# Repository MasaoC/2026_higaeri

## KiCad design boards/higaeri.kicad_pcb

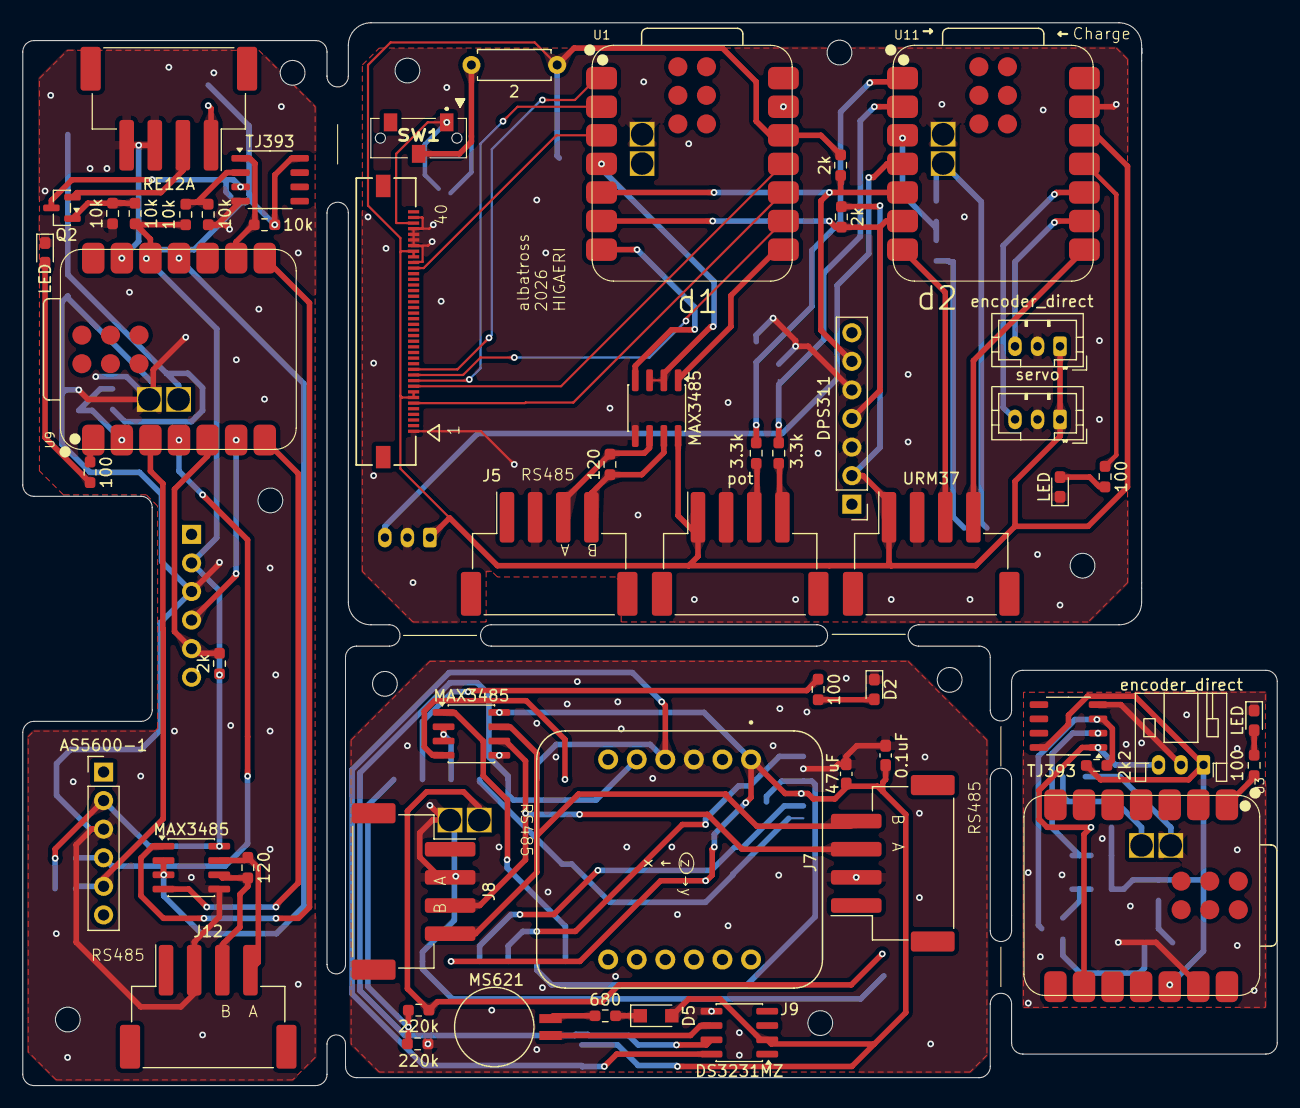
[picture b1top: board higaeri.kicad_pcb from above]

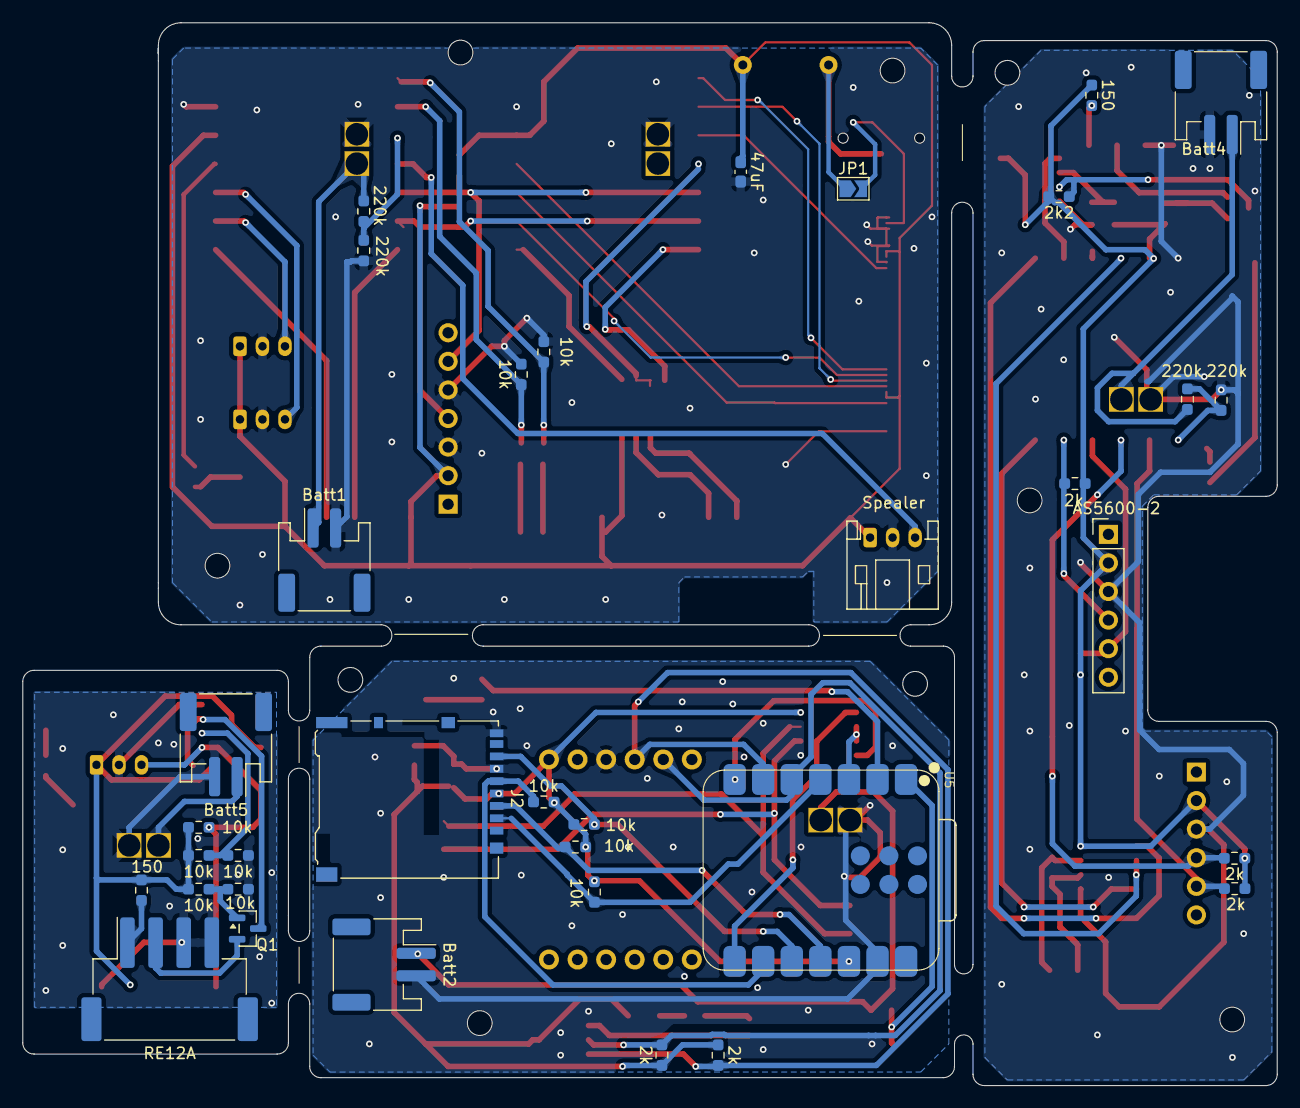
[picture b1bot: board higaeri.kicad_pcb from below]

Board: 2 copper layers, 111.5 x 94.4 mm, 90 parts (35 on the bottom side), 82 nets.

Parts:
AS5600-1: AoS; PinHeader_1x06_P2.54mm_Vertical
AS5600-2: AoA; PinHeader_1x06_P2.54mm_Vertical
BT2: MS621; BatteryHolder_Seiko_MS621F
Batt1, Batt2, Batt4, Batt5: Conn_01x02; JST_PH_S2B-PH-SM4-TB_1x02-1MP_P2.00mm_Horizontal
C1: 0.1uF; C_0603_1608Metric_Pad1.08x0.95mm_HandSolder
C2, C3: 47uF; C_0603_1608Metric_Pad1.08x0.95mm_HandSolder
D1, D2, D3, D4: LED; LED_0603_1608Metric_Pad1.05x0.95mm_HandSolder
D5: D; Nexperia_CFP3_SOD-123W
DPS311: Adafruit DPS310; PinHeader_1x07_P2.54mm_Vertical
J1: 5051104096; CON_5051104096_MOL
J2: Micro_SD_Card; microSD_HC_Hirose_DM3AT-SF-PEJM5
J3: URM37; JST_XH_S4B-XH-SM4-TB_1x04-1MP_P2.50mm_Horizontal
J4: servo; JST_PH_B3B-PH-K_1x03_P2.00mm_Vertical
J5: RS485_TFT; JST_XH_S4B-XH-SM4-TB_1x04-1MP_P2.50mm_Horizontal
J6: encoder_direct; JST_PH_B3B-PH-K_1x03_P2.00mm_Vertical
J7: RS485_logger_2; JST_XH_S4B-XH-SM4-TB_1x04-1MP_P2.50mm_Horizontal
J8: RS485_logger; JST_XH_S4B-XH-SM4-TB_1x04-1MP_P2.50mm_Horizontal
J9: BNO085; MODULE_4754_without_holes
J10: pot; JST_XH_S4B-XH-SM4-TB_1x04-1MP_P2.50mm_Horizontal
J11, J14: RE12A; JST_XH_S4B-XH-SM4-TB_1x04-1MP_P2.50mm_Horizontal
J12: RS485_airdata; JST_XH_S4B-XH-SM4-TB_1x04-1MP_P2.50mm_Horizontal
J13: Conn_01x03 speaker; JST_PH_S3B-PH-K_1x03_P2.00mm_Horizontal
J15: encoder_direct; JST_PH_S3B-PH-K_1x03_P2.00mm_Horizontal
JP1: SolderJumper_2_Open; SolderJumper-2_P1.3mm_Open_TrianglePad1.0x1.5mm
Q1, Q2: NPN; SOT-23
R1, R2, R3, R9, R13, R18, R19, R21, R37, R38, R40, R41, R42, R44, R45, R46: 10k; R_0603_1608Metric_Pad0.98x0.95mm_HandSolder
R4: 680; R_0603_1608Metric_Pad0.98x0.95mm_HandSolder
R5, R32: 120; R_0603_1608Metric_Pad0.98x0.95mm_HandSolder
R6, R7, R8, R11, R12, R14, R25, R27: 2k; R_0603_1608Metric_Pad0.98x0.95mm_HandSolder
R10, R20: 3.3k; R_0603_1608Metric_Pad0.98x0.95mm_HandSolder
R15, R22, R23, R31: 100; R_0603_1608Metric_Pad0.98x0.95mm_HandSolder
R16, R43: 2k2; R_0603_1608Metric_Pad0.98x0.95mm_HandSolder
R17: 2; R_Axial_DIN0207_L6.3mm_D2.5mm_P7.62mm_Horizontal
R24, R28, R33, R34, R35, R36: 220k; R_0603_1608Metric_Pad0.98x0.95mm_HandSolder
R26, R39: 150; R_0603_1608Metric_Pad0.98x0.95mm_HandSolder
SW1: SW_DIP_x01; CLSB12A02T
U1: MOUDLE-SEEEDUINO-XIAO-ESP32C3_TFT; XIAO-ESP32C3-SMD_battery_handsolder
U2, U4, U8: MAX3485; SOIC-8_3.9x4.9mm_P1.27mm
U3, U9: MOUDLE-SEEEDUINO-XIAO-ESP32C3_airdata; XIAO-ESP32C3-SMD_battery_handsolder
U5: MOUDLE-SEEEDUINO-XIAO-ESP32C3_logger; XIAO-ESP32C3-SMD_battery_handsolder
U6: DS3231MZ; SOIC-8_3.9x4.9mm_P1.27mm
U7, U10: TJ393; SOP-8_3.9x4.9mm_P1.27mm
U11: MOUDLE-SEEEDUINO-XIAO-ESP32C3_pot; XIAO-ESP32C3-SMD_battery_handsolder

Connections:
+3.3V-1: AS5600-1.2 (3V3), AS5600-2.2 (3V3), R6.1, R14.1, R25.1, R26.1, R27.1, R41.1, R43.1, R44.1, R46.1, U8.8 (VCC), U9.12 (3V3), U10.8 (V+)
+3.3V-2: C1.1, C2.1, D5.2 (A), J2.4 (VDD), J9.JP1_1 (VIN), R1.2, R2.2, R3.2, R7.1, R8.1, R13.2, U2.8 (VCC), U5.12 (3V3), U6.2 (VCC)
+3.3V-3: C3.1, DPS311.2 (3Vo), J1.7, J1.8, J1.32, J1.33, J3.1, J4.1, J6.1, J10.1, J13.1, R11.2, R12.1, R17.1, U1.12 (3V3), U4.8 (VCC), U11.12 (3V3)
+3.3V-4: J15.1, R16.1, R19.1, R37.1, R39.1, R40.1, U3.12 (3V3), U7.8 (V+)
+BATT-1: Batt4.1, R35.1, U9.15 (BAT)
+BATT-2: Batt2.1, R33.1, U5.15 (BAT)
+BATT-3: Batt1.1, R24.1, U11.15 (BAT)
+BATT-4: Batt5.1, U3.15 (BAT)
/1. airdata/DE/RE: U8.2 (~RE), U8.3 (DE), U9.11 (GPIO10_D10_MOSI)
/1. airdata/RS485_A: J12.3, R32.2, U8.6 (A)
/1. airdata/RS485_B: J12.4, R32.1, U8.7 (B)
/1. airdata/SCL: AS5600-2.4 (SCL), R6.2, U9.6 (GPIO7_D5_SCL)
/1. airdata/SCL_soft: AS5600-1.4 (SCL), R25.2, U9.4 (GPIO5_A3_D3)
/1. airdata/SDA: AS5600-2.5 (SDA), R14.2, U9.5 (GPIO6_D4_SDA)
/1. airdata/SDA_soft: AS5600-1.5 (SDA), R27.2, U9.3 (GPIO4_A2_D2)
/1. airdata/V_check-1: R35.2, R36.1, U9.2 (GPIO3_A1_D1)
/1. airdata/encoder_collector: J11.2, Q2.2 (E)
/1. airdata/encoder_out: R46.2, U9.9 (GPIO8_D8_SCK), U10.1
/1. airdata/input: Q2.3 (C), R43.2, U10.3 (+)
/2.logger/CS: J2.2 (DAT3/CD), R2.1, U5.4 (GPIO5_A3_D3)
/2.logger/DE/RE: U2.2 (~RE), U2.3 (DE), U5.3 (GPIO4_A2_D2)
/2.logger/MISO: J2.7 (DAT0), R3.1, U5.10 (GPIO9_D9_MISO)
/2.logger/MOSI: J2.3 (CMD), R1.1, U5.11 (GPIO10_D10_MOSI)
/2.logger/SCL: J9.JP1_4 (SCL), R8.2, U5.6 (GPIO7_D5_SCL), U6.8 (SCL)
/2.logger/SCLK: J2.5 (CLK), R13.1, U5.9 (GPIO8_D8_SCK)
/2.logger/SDA: J9.JP1_5 (SDA), R7.2, U5.5 (GPIO6_D4_SDA), U6.7 (SDA)
/2.logger/V_check-2: R33.2, R34.1, U5.1 (GPIO2_A0_D0)
/3. TFT/CS: J1.10, U1.2 (GPIO3_A1_D1)
/3. TFT/DCX-SCLK: J1.11, U1.9 (GPIO8_D8_SCK)
/3. TFT/DE/RE: U1.4 (GPIO5_A3_D3), U4.2 (~RE), U4.3 (DE)
/3. TFT/Pot_elv: R9.1, R10.1, U11.1 (GPIO2_A0_D0)
/3. TFT/Pot_rud: R18.1, R20.1, U11.2 (GPIO3_A1_D1)
/3. TFT/RES: J1.30, U1.3 (GPIO4_A2_D2)
/3. TFT/RS485_A: J5.3, R5.2, U4.6 (A)
/3. TFT/RS485_B: J5.4, R5.1, U4.7 (B)
/3. TFT/RX: J3.4, U11.8 (GPIO20_D7_RX)
/3. TFT/RX_encoder: J6.3, U11.9 (GPIO8_D8_SCK)
/3. TFT/SCL: DPS311.4 (SCK), R12.2, U1.6 (GPIO7_D5_SCL), U11.6 (GPIO7_D5_SCL)
/3. TFT/SDA: DPS311.6 (SDI), R11.1, U1.5 (GPIO6_D4_SDA), U11.5 (GPIO6_D4_SDA)
/3. TFT/SDA-MOSI: J1.9, U1.11 (GPIO10_D10_MOSI)
/3. TFT/SDO-MISO: J1.6, U1.10 (GPIO9_D9_MISO)
/3. TFT/Speaker: J13.3, U11.4 (GPIO5_A3_D3)
/3. TFT/TX: J3.3, U11.7 (GPIO21_D6_TX)
/3. TFT/V_check-3: R24.2, R28.1, U11.3 (GPIO4_A2_D2)
/3. TFT/WRX-D/C: J1.12, U1.1 (GPIO2_A0_D0)
/3. TFT/servo: J4.3, U11.10 (GPIO9_D9_MISO)
/RE12A_amplifier/encoder_anode: J14.1, R39.2
/RE12A_amplifier/encoder_collector: J14.2, Q1.2 (E)
/RE12A_amplifier/encoder_out: J15.3, R40.2, U3.9 (GPIO8_D8_SCK), U7.1
/RE12A_amplifier/input: Q1.3 (C), R16.2, U7.3 (+)
GND-1: AS5600-1.3 (GND), AS5600-2.3 (GND), Batt4.2, D4.1 (K), J11.3, J11.4, J12.2, R36.2, R42.2, R45.2, U8.5 (GND), U9.13 (GND), U9.16 (GND), U10.4 (V-)
GND-2: Batt2.2, C1.2, C2.2, D2.1 (K), J2.6 (VSS), J2.9 (SHIELD), J7.2, J8.2, J9.JP1_3 (GND), R34.2, U2.5 (GND), U5.13 (GND), U5.16 (GND), U6.5 (GND)
GND-3: Batt1.2, C3.2, D1.1 (K), DPS311.3 (GND), DPS311.5 (SDO), J1.1, J1.31, J1.34, J1.35, J1.36, J1.37, J1.39, J3.2, J4.2, J5.2, J6.2, J10.2, J13.2, R9.2, R18.2, R28.2, U1.13 (GND), U1.16 (GND), U4.5 (GND), U11.13 (GND), U11.16 (GND)
GND-4: Batt5.2, D3.1 (K), J14.3, J14.4, J15.2, R21.2, R38.2, U3.13 (GND), U3.16 (GND), U7.4 (V-)
unnamed: BT2.1 (+), R4.1
unnamed: BT2.2 (-), U6.6 (VBAT)
unnamed: D1.2 (A), R23.2
unnamed: D2.2 (A), R22.2
unnamed: D3.2 (A), R15.2
unnamed: D4.2 (A), R31.2
unnamed: D5.1 (K), R4.2
unnamed: J10.3, R10.2
unnamed: J10.4, R20.2
unnamed: J11.1, R26.2
unnamed: JP1.1 (A), R17.2, SW1.2
unnamed: J1.38, JP1.2 (B), SW1.1
unnamed: Q1.1 (B), R19.2, R21.1
unnamed: Q2.1 (B), R41.2, R42.1
unnamed: U1.8 (GPIO20_D7_RX), U4.1 (RO)
unnamed: U1.7 (GPIO21_D6_TX), U4.4 (DI)
unnamed: U2.4 (DI), U5.7 (GPIO21_D6_TX)
unnamed: U2.1 (RO), U5.8 (GPIO20_D7_RX)
unnamed: R15.1, U3.1 (GPIO2_A0_D0)
unnamed: R22.1, U5.2 (GPIO3_A1_D1)
unnamed: R37.2, R38.1, U7.2 (-)
unnamed: U8.4 (DI), U9.7 (GPIO21_D6_TX)
unnamed: U8.1 (RO), U9.8 (GPIO20_D7_RX)
unnamed: R31.1, U9.1 (GPIO2_A0_D0)
unnamed: R44.2, R45.1, U10.2 (-)
unnamed: R23.1, U11.11 (GPIO10_D10_MOSI)
RS485_A: J7.3, J8.3, U2.6 (A)
RS485_B: J7.4, J8.4, U2.7 (B)

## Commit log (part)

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2026-06-13 高度計の補正以外完了
